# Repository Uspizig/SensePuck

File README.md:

# SensePuck: The Addon Board for the Seeed Round Display

## Features:

1. **AudioAmplifier MAX98357**: Listen to your favourite Tunes with an Audio Amplifier

2. **I2C Connector for Sensor**: Connect your favourite I2C Sensor board with the embedded 2.54mm connector

3. **Wireless Control**: Untehther your development process with the wireless capabilities. With WiFi and BLE, this tool allows remote control and data logging. Users can adjust settings and monitor data from a distance, offering a more flexible development experience.

4. **LIS3M Magentometer**: Check your Heading

5. **LSM6 Gyro+ACC**: Check Movements, Steps Pedometer

5. **Open Source & Programmable**: As an open-source device, the Device offers unmatched versatility. It is fully programmable, allowing you to tailor its functionality to your specific applications. This customization extends to software and hardware, opening up endless possibilities for creative and efficient project development.

6. **Compact Design**: Designed for convenience, the LoRaCam Board compact and sleek form factor allows for seamless integration into existing setups. Its compatibility with USB PD power sources and inline integration capability minimizes the need for additional equipment or extensive redesign, making it a versatile and user-friendly addition to any development environment.

7. **Display+Touchscreeen**: Monitor live the current status on the Seeed Display

8. **RTC**: RealTimeClock from the Seeed Display

9. **RGB LED**: Status LED

10. **Battery Charger** Use the Battery Charger on the Seeed Display

11. **Rotary Encoder** Perfect for switching the Radio Station

12.  BME680: Measure Temperature, Humidity, Air Pressure, TVOC, eCO² (might update to BME688 or BME690 soon)
    
## Specifications

Needed Libaries:

https://github.com/schreibfaul1/ESP32-audioI2S
https://github.com/pololu/lis3mdl-arduino
https://github.com/pololu/lsm6-arduino
https://github.com/Seeed-Projects/SeeedStudio_TFT_eSPI
https://github.com/Seeed-Projects/SeeedStudio_lvgl
https://github.com/Seeed-Studio/Seeed_Arduino_RoundDisplay

### Key Features:

### Future Developments:

AI Detection of objects and determine if the device shall sent the data via LoRa 

## Testing for Performance

At the heart of SensePuck's design is a commitment to reliability and performance. To ensure that SensePuck stands up to real-world demands, we subjected it to testing under use conditions.

## License

MIT License

Copyright (c) 2025 blue2monster

Permission is hereby granted, free of charge, to any person obtaining a copy
of this software and associated documentation files (the "Software"), to deal
in the Software without restriction, including without limitation the rights
to use, copy, modify, merge, publish, distribute, sublicense, and/or sell
copies of the Software, and to permit persons to whom the Software is
furnished to do so, subject to the following conditions:

The above copyright notice and this permission notice shall be included in all
copies or substantial portions of the Software.

THE SOFTWARE IS PROVIDED "AS IS", WITHOUT WARRANTY OF ANY KIND, EXPRESS OR
IMPLIED, INCLUDING BUT NOT LIMITED TO THE WARRANTIES OF MERCHANTABILITY,
FITNESS FOR A PARTICULAR PURPOSE AND NONINFRINGEMENT. IN NO EVENT SHALL THE
AUTHORS OR COPYRIGHT HOLDERS BE LIABLE FOR ANY CLAIM, DAMAGES OR OTHER
LIABILITY, WHETHER IN AN ACTION OF CONTRACT, TORT OR OTHERWISE, ARISING FROM,
OUT OF OR IN CONNECTION WITH THE SOFTWARE OR THE USE OR OTHER DEALINGS IN THE
SOFTWARE.

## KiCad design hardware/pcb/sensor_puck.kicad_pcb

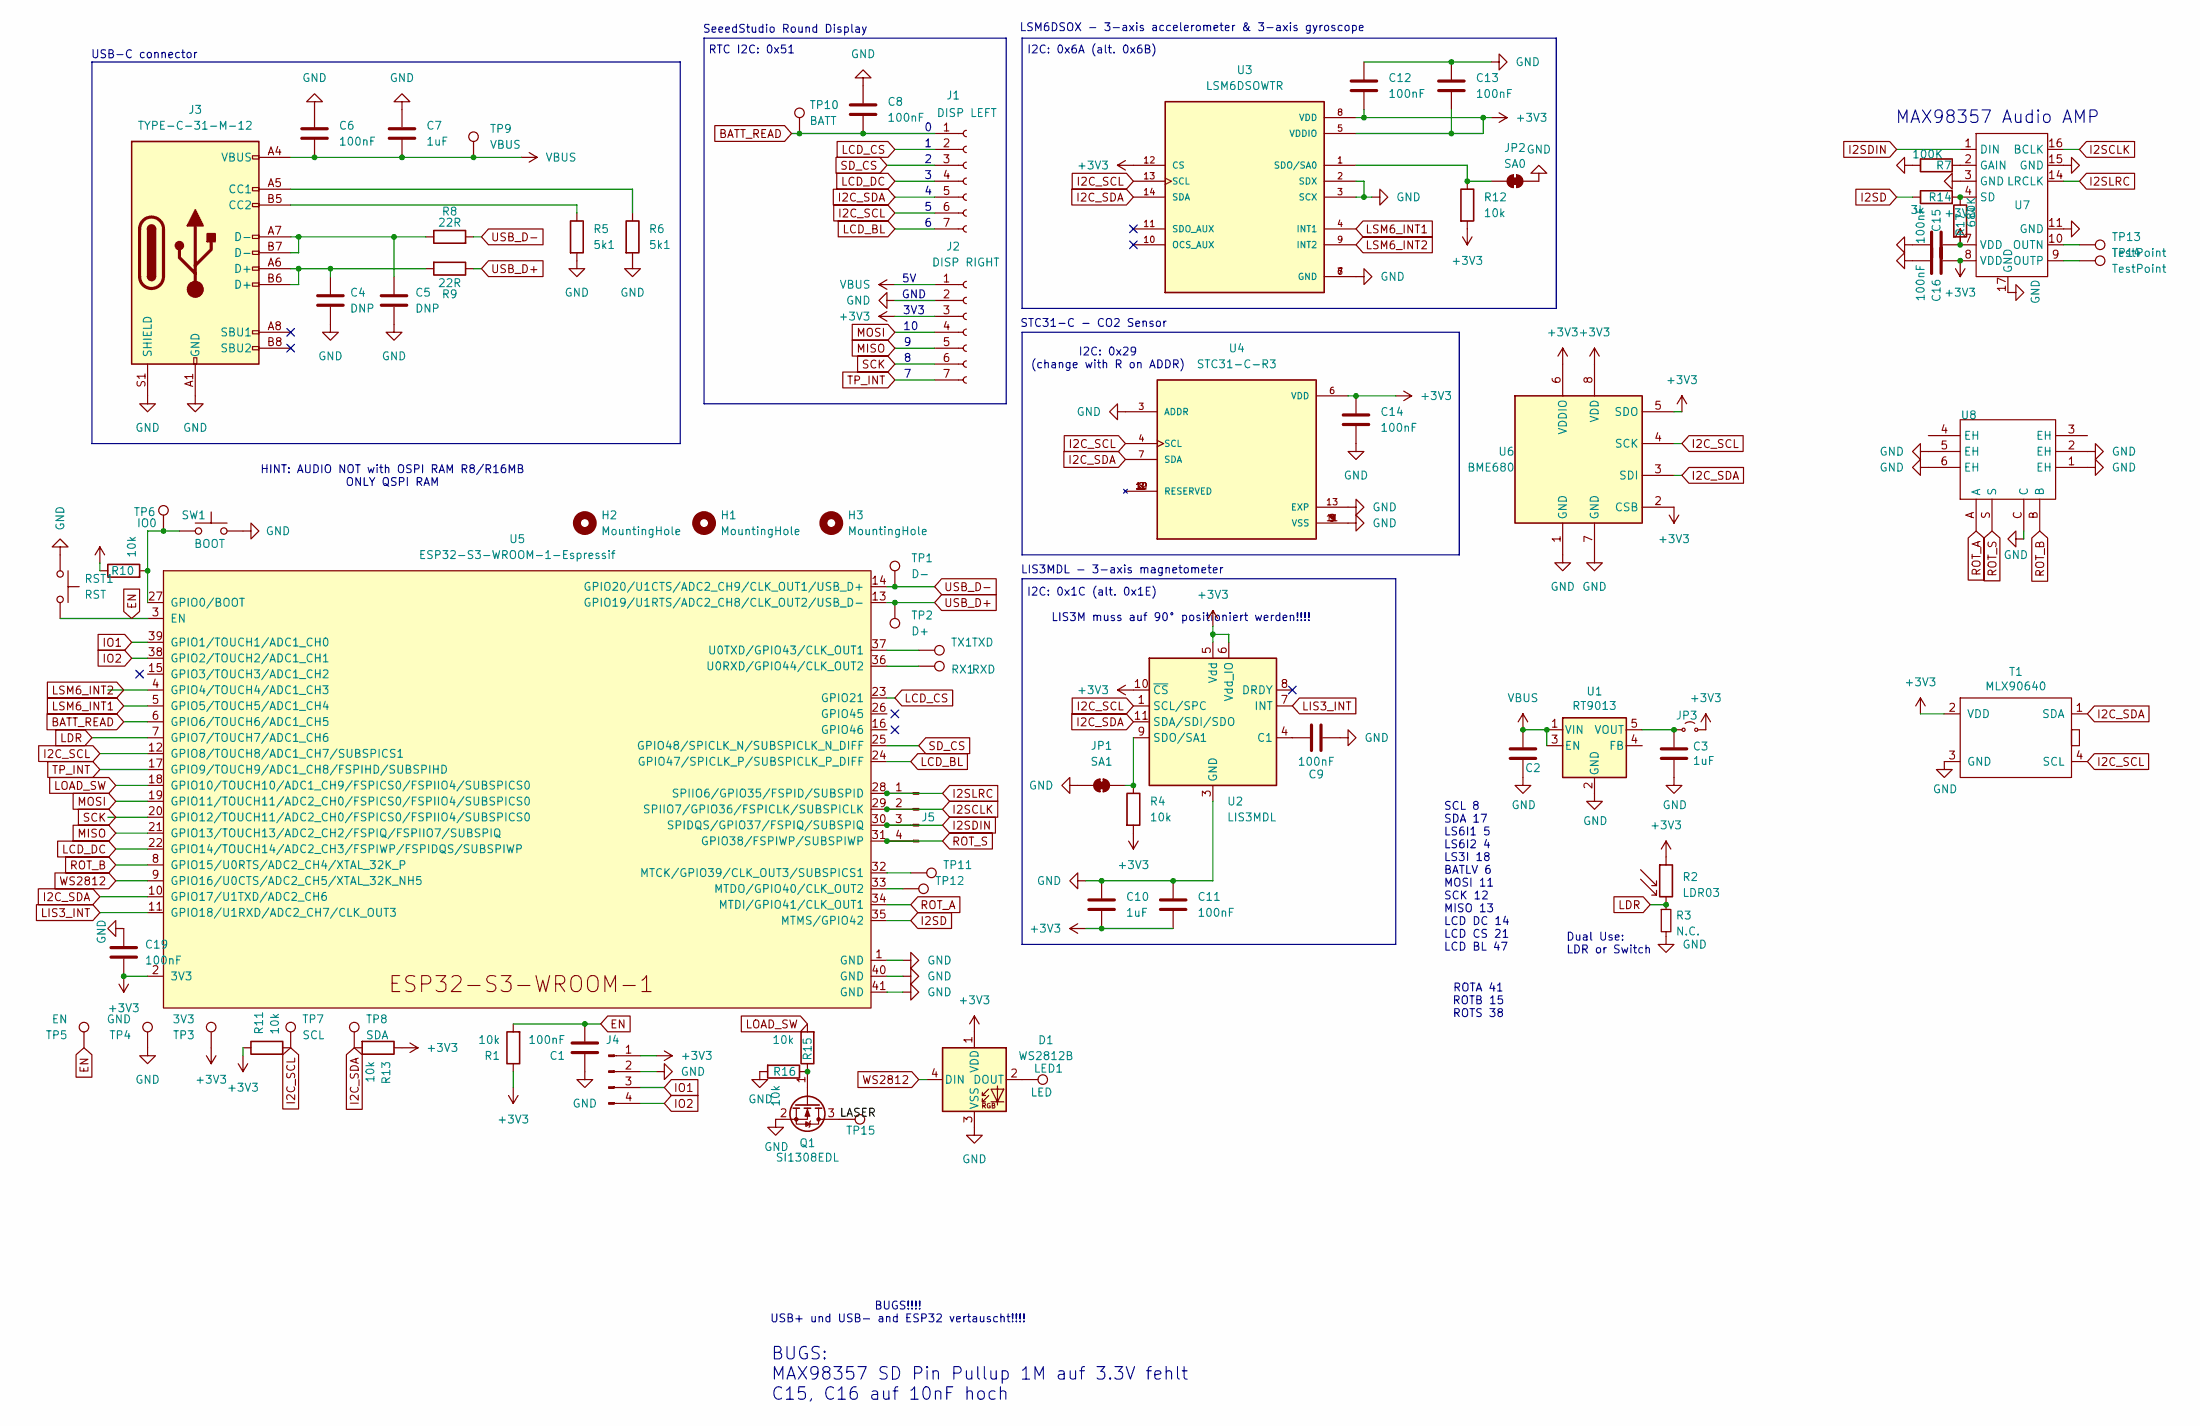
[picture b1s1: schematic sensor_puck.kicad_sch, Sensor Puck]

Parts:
C1, C6, C8, C9, C11, C12, C13, C14, C19: 100nF; C_0805_2012Metric
C2, C3: 1uF; C_0805_2012Metric_Pad1.18x1.45mm_HandSolder
C4, C5: DNP; C_0805_2012Metric
C7, C10: 1uF; C_0805_2012Metric
C15, C16: 100nF; C_0805_2012Metric_Pad1.18x1.45mm_HandSolder
D1: WS2812B; LED_WS2812B_PLCC4_5.0x5.0mm_P3.2mm
H1, H2: MountingHole; baerklein
H3: MountingHole; MountingHole_2.2mm_M2
J1: DISP LEFT; PinHeader_1x07_P2.54mm_Vertical
J2: DISP RIGHT; PinHeader_1x07_P2.54mm_Vertical
J3: TYPE-C-31-M-12; USB-C_SMD-TYPE-C-31-M-12
J4: Conn_01x04_Pin; PinHeader_1x04_P2.54mm_Vertical_SMD_Pin1Left
J5: Conn_01x04_Pin; PinHeader_1x04_P1.00mm_Vertical
JP1: SA1; SolderJumper-2_P1.3mm_Open_RoundedPad1.0x1.5mm
JP2: SA0; SolderJumper-2_P1.3mm_Open_RoundedPad1.0x1.5mm
JP3: Jumper_2_Small_Open; SolderJumper-2_P1.3mm_Open_RoundedPad1.0x1.5mm
LED1: LED; TestPoint_Pad_1.5x1.5mm
Q1: SI1308EDL; SOT-323_SC-70
R1, R15, R16: 10k; R_0603_1608Metric_Pad0.98x0.95mm_HandSolder
R2: LDR03; R_LDR_10x8.5mm_P7.6mm_Vertical
R3: N.C.; R_0805_2012Metric_Pad1.20x1.40mm_HandSolder
R4, R10, R11, R12, R13: 10k; R_0805_2012Metric
R5, R6: 5k1; R_0805_2012Metric
R7: 100K; R_0805_2012Metric_Pad1.20x1.40mm_HandSolder
R8, R9: 22R; R_0805_2012Metric
R14: 3k; R_0805_2012Metric_Pad1.20x1.40mm_HandSolder
R17: 680K; R_0805_2012Metric_Pad1.20x1.40mm_HandSolder
RST1: RST; SW_PUSH_6mm
RX1: RXD; TestPoint_Pad_1.0x1.0mm
SW1: BOOT; SW_PUSH_6mm
T1: MLX90640; Part Number 482-MLX90640ESFBABSP
TP1: D-; TestPoint_Pad_1.0x1.0mm
TP2: D+; TestPoint_Pad_1.0x1.0mm
TP3: 3V3; TestPoint_Pad_1.0x1.0mm
TP4: GND; TestPoint_Pad_1.0x1.0mm
TP5: EN; TestPoint_Pad_1.0x1.0mm
TP6: IO0; TestPoint_Pad_1.0x1.0mm
TP7: SCL; TestPoint_Pad_1.0x1.0mm
TP8: SDA; TestPoint_Pad_1.0x1.0mm
TP9: VBUS; TestPoint_Pad_1.0x1.0mm
TP10: BATT; TestPoint_Pad_1.0x1.0mm
TP11, TP12, TP13, TP14, TP15: TestPoint; TestPoint_Pad_D1.0mm
TX1: TXD; TestPoint_Pad_1.0x1.0mm
U1: RT9013; SOT-23-5
U2: LIS3MDL; LGA-12_2x2mm_P0.5mm
U3: LSM6DSOWTR; LGA-14_3x2.5mm_P0.5mm_LayoutBorder3x4y; PARTREV 3.0
U4: STC31-C-R3; XDCR_STC31-C-R3; PARTREV 3.2
U5: ESP32-S3-WROOM-1-Espressif; ESP32-S3-WROOM-1
U6: BME680; Bosch_LGA-8_3x3mm_P0.8mm_ClockwisePinNumbering
U7: TQFN-16_L3.0-W3.0-P0.50-BL-EP1.5
U8: SW-SMD_SIQ-02FVS3_1; Manufacturer Part SIQ-02FVS3; LCSC Part Name 拨轮滚轮旋转编码器开关

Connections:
+3V3: C10.2, C11.2, C12.2, C13.2, C14.1, C15.1, C16.1, C19.2, D1.1 (VDD), J2.3, J4.1, JP3.2 (B), R1.1, R2.1, R4.2, R10.1, R11.1, R12.2, R13.1, R17.2, T1.2 (VDD), TP3.1, U2.5 (Vdd), U2.6 (Vdd_IO), U2.10 (~CS), U3.5 (VDDIO), U3.8 (VDD), U3.12 (CS), U4.6 (VDD), U5.2 (3V3), U6.2 (CSB), U6.5 (SDO), U6.6 (VDDIO), U6.8 (VDD), U7.7 (VDD), U7.8 (VDD)
/LASER: Q1.3 (D), TP15.1; also elsewhere on the board
BATT_READ: C8.1, J1.1, TP10.1, U5.6 (GPIO6/TOUCH6/ADC1_CH5)
EN: C1.2, R1.2, RST1.2, TP5.1, U5.3 (EN); also elsewhere on the board
GND: C1.1, C2.1, C3.1, C4.2, C5.2, C6.1, C7.1, C8.2, C9.2, C10.1, C11.1, C12.1, C13.1, C14.2, C15.2, C16.2, C19.1, D1.3 (VSS), J2.2, J3.A1 (GND), J3.A12 (GND), J3.B1 (GND), J3.B12 (GND), J3.S1 (SHIELD), J4.2, JP1.1 (A), JP2.2 (B), Q1.2 (S), R3.2, R5.2, R6.2, R7.1, R16.2, RST1.1, SW1.2, T1.3 (GND), TP4.1, U1.2 (GND), U2.2 (GND), U2.3 (GND), U2.12 (GND), U3.2 (SDX), U3.3 (SCX), U3.6 (GND), U3.7 (GND), U4.1 (VSS), U4.3 (ADDR), U4.5 (VSS), U4.9 (VSS), U4.11 (VSS), U4.13 (EXP), U5.1 (GND), U5.40 (GND), U5.41 (GND), U6.1 (GND), U6.7 (GND), U7.3 (GND), U7.11 (GND), U7.15 (GND), U7.17 (GND), U8.1 (EH), U8.2 (EH), U8.5 (EH), U8.6 (EH), U8.C; also elsewhere on the board
I2C_SCL: J1.6, R11.2, T1.4 (SCL), TP7.1, U2.1 (SCL/SPC), U3.13 (SCL), U4.4 (SCL), U5.12 (GPIO8/TOUCH8/ADC1_CH7/SUBSPICS1), U6.4 (SCK)
I2C_SDA: J1.5, R13.2, T1.1 (SDA), TP8.1, U2.11 (SDA/SDI/SDO), U3.14 (SDA), U4.7 (SDA), U5.10 (GPIO17/U1TXD/ADC2_CH6), U6.3 (SDI)
I2SCLK: J5.2, U5.29 (SPIIO7/GPIO36/FSPICLK/SUBSPICLK), U7.16 (BCLK)
I2SD: R14.1, U5.35 (MTMS/GPIO42)
I2SDIN: J5.3, U5.30 (SPIDQS/GPIO37/FSPIQ/SUBSPIQ), U7.1 (DIN)
I2SLRC: J5.1, U5.28 (SPIIO6/GPIO35/FSPID/SUBSPID), U7.14 (LRCLK)
IO1: J4.3, U5.39 (GPIO1/TOUCH1/ADC1_CH0)
IO2: J4.4, U5.38 (GPIO2/TOUCH2/ADC1_CH1)
LCD_BL: J1.7, U5.24 (GPIO47/SPICLK_P/SUBSPICLK_P_DIFF)
LCD_CS: J1.2, U5.23 (GPIO21)
LCD_DC: J1.4, U5.22 (GPIO14/TOUCH14/ADC2_CH3/FSPIWP/FSPIDQS/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)
LDR: R2.2, R3.1, U5.7 (GPIO7/TOUCH7/ADC1_CH6)
LIS3_INT: U2.7 (INT), U5.11 (GPIO18/U1RXD/ADC2_CH7/CLK_OUT3)
LOAD_SW: R15.2, U5.18 (GPIO10/TOUCH10/ADC1_CH9/FSPICS0/FSPIIO4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)
LSM6_INT1: U3.4 (INT1), U5.5 (GPIO5/TOUCH5/ADC1_CH4)
LSM6_INT2: U3.9 (INT2), U5.4 (GPIO4/TOUCH4/ADC1_CH3)
MISO: J2.5, U5.21 (GPIO13/TOUCH13/ADC2_CH2/FSPIQ/FSPIIO7/S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)
MOSI: J2.4, U5.19 (GPIO11/TOUCH11/ADC2_CH0/FSPICS0/FSPIIO4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)
unnamed: C4.1, J3.A6 (D+), J3.B6 (D+), R9.2
unnamed: C5.1, J3.A7 (D-), J3.B7 (D-), R8.1
unnamed 25: D1.2 (DOUT), LED1.1; also elsewhere on the board
unnamed: J3.A5 (CC1), R6.1
unnamed: J3.B5 (CC2), R5.1
unnamed: JP1.2 (B), R4.1, U2.9 (SDO/SA1)
unnamed: JP2.1 (A), R12.1, U3.1 (SDO/SA0)
unnamed: C3.2, JP3.1 (A), U1.5 (VOUT)
unnamed: Q1.1 (G), R15.1, R16.1
unnamed: C9.1, U2.4 (C1)
unnamed: R10.2, SW1.1, TP6.1, U5.27 (GPIO0/BOOT)
unnamed: TP11.1, U5.32 (MTCK/GPIO39/CLK_OUT3/SUBSPICS1)
unnamed: TP12.1, U5.33 (MTDO/GPIO40/CLK_OUT2)
unnamed 36: RX1.1, U5.36 (U0RXD/GPIO44/CLK_OUT2); also elsewhere on the board
unnamed 37: TX1.1, U5.37 (U0TXD/GPIO43/CLK_OUT1); also elsewhere on the board
unnamed: R7.2, U7.2 (GAIN)
unnamed: TP13.1, U7.10 (OUTN)
unnamed: TP14.1, U7.9 (OUTP)
unnamed: R14.2, R17.1, U7.4 (SD)
ROT_A: U5.34 (MTDI/GPIO41/CLK_OUT1), U8.A
ROT_B: U5.8 (GPIO15/U0RTS/ADC2_CH4/XTAL_32K_P), U8.B
ROT_S: J5.4, U5.31 (GPIO38/FSPIWP/SUBSPIWP), U8.S
SCK: J2.6, U5.20 (GPIO12/TOUCH11/ADC2_CH0/FSPICS0/FSPIIO4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)
SD_CS: J1.3, U5.25 (GPIO48/SPICLK_N/SUBSPICLK_N_DIFF)
TP_INT: J2.7, U5.17 (GPIO9/TOUCH9/ADC1_CH8/FSPIHD/SUBSPIHD)
USB_D+: R9.1, TP2.1, U5.13 (GPIO19/U1RTS/ADC2_CH8/CLK_OUT2/USB_D-)
USB_D-: R8.2, TP1.1, U5.14 (GPIO20/U1CTS/ADC2_CH9/CLK_OUT1/USB_D+)
VBUS: C2.2, C6.2, C7.2, J2.1, J3.A4 (VBUS), J3.A9 (VBUS), J3.B4 (VBUS), J3.B9 (VBUS), TP9.1, U1.1 (VIN), U1.3 (EN)
WS2812: D1.4 (DIN), U5.9 (GPIO16/U0CTS/ADC2_CH5/XTAL_32K_NH5)

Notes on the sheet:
USB-C connector
BUGS: MAX98357 SD Pin Pullup 1M auf 3.3V fehlt C15, C16 auf 10nF hoch
LIS3M muss auf 90° positioniert werden!!!!
SeeedStudio Round Display
SCL 8 SDA 17 LS6I1 5 LS6I2 4 LS3I 18 BATLV 6 MOSI 11 SCK 12 MISO 13 LCD DC 14 LCD CS 21 LCD BL 47
I2C: 0x1C (alt. 0x1E)
RTC I2C: 0x51
Dual Use: LDR or Switch
I2C: 0x6A (alt. 0x6B)
BUGS!!!! USB+ und USB- and ESP32 vertauscht!!!!
LIS3MDL - 3-axis magnetometer
STC31-C - CO2 Sensor
GND
LSM6DSOX - 3-axis accelerometer & 3-axis gyroscope
ROTA 41 ROTB 15 ROTS 38
3V3
I2C: 0x29 (change with R on ADDR)
MAX98357 Audio AMP
HINT: AUDIO NOT with OSPI RAM R8/R16MB ONLY QSPI RAM

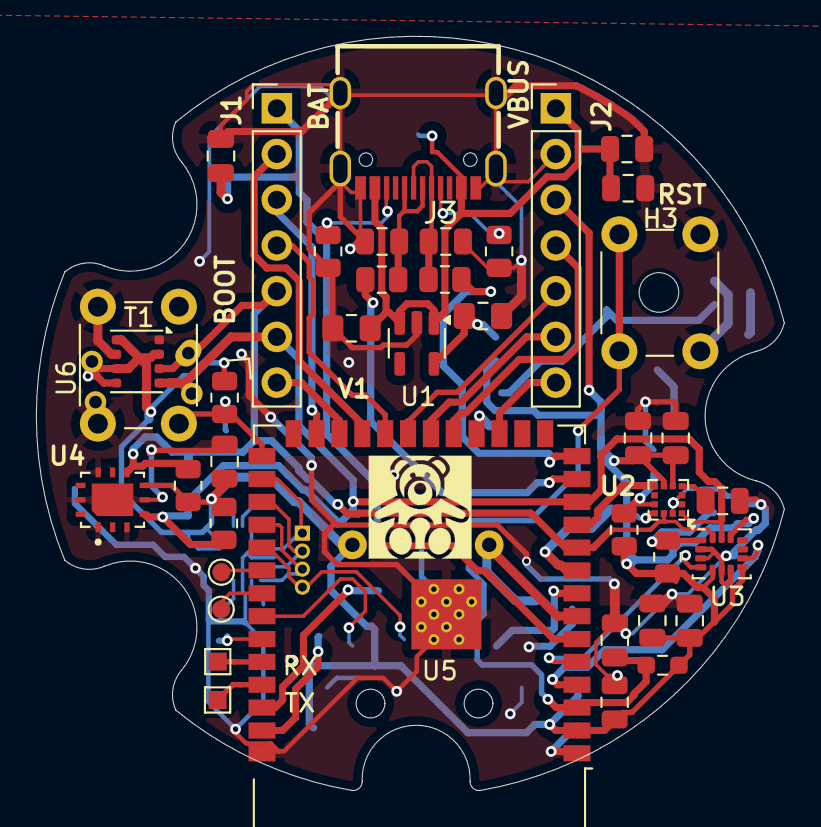
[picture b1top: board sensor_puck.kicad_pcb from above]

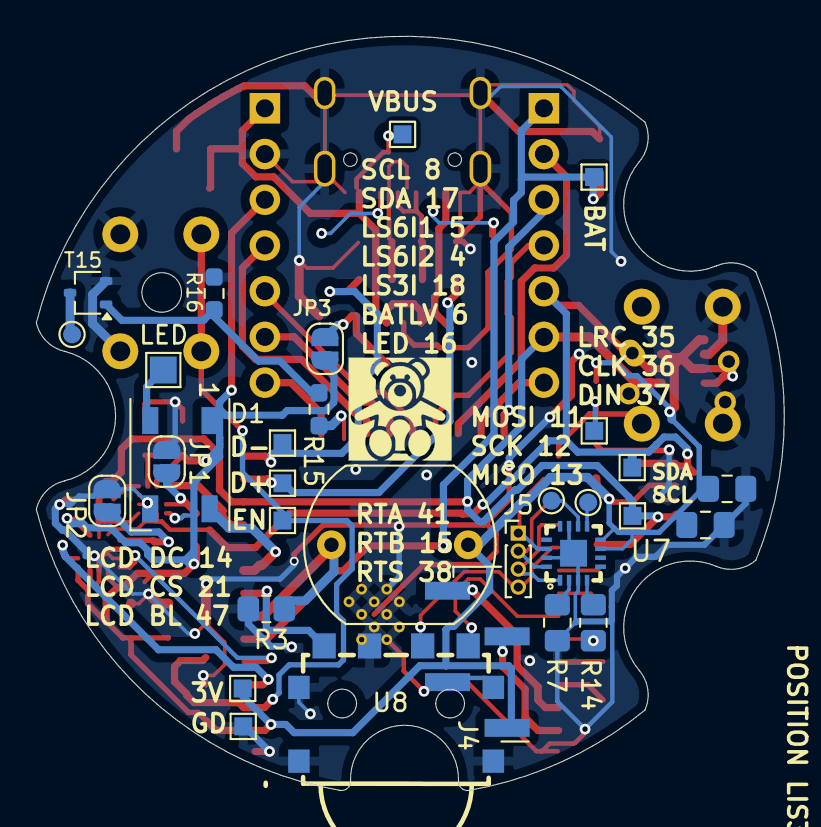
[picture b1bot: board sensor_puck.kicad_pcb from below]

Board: 2 copper layers, 41.6 x 41.9 mm, 75 parts (32 on the bottom side), 52 nets.

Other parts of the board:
LED: LED; TestPoint_Pad_1.5x1.5mm
RST: RST; SW_PUSH_6mm
RX: RXD; TestPoint_Pad_1.0x1.0mm
T15: TestPoint; TestPoint_Pad_D1.0mm
TX: TXD; TestPoint_Pad_1.0x1.0mm

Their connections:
/LASER: T15.1; also elsewhere on the board
EN: RST.2; also elsewhere on the board
GND: RST.1; also elsewhere on the board
unnamed 25: LED.1; also elsewhere on the board
unnamed 36: RX.1; also elsewhere on the board
unnamed 37: TX.1; also elsewhere on the board

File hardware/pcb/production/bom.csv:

Designator,Footprint,Quantity,Value,LCSC Part #
"C1, C11, C12, C13, C14, C15, C16, C19, C6, C8, C9",0805,11,100nF,
"C10, C2, C3, C7",0805,4,1uF,
"C4, C5",0805,2,DNP,
D1,LED_WS2812B_PLCC4_5.0x5.0mm_P3.2mm,1,WS2812B,
J1,PinHeader_1x07_P2.54mm_Vertical,1,DISP LEFT,
J2,PinHeader_1x07_P2.54mm_Vertical,1,DISP RIGHT,
J3,USB-C_SMD-TYPE-C-31-M-12,1,TYPE-C-31-M-12,
J4,PinHeader_1x04_P2.54mm_Vertical_SMD_Pin1Left,1,Conn_01x04_Pin,
J5,PinHeader_1x04_P1.00mm_Vertical,1,Conn_01x04_Pin,
JP3,SolderJumper-2_P1.3mm_Open_RoundedPad1.0x1.5mm,1,Jumper_2_Small_Open,
LED,TestPoint_Pad_1.5x1.5mm,1,LED,
Q1,SOT-323_SC-70,1,SI1308EDL,
"R1, R15, R16",0603,3,10k,
"R10, R11, R12, R13, R4",0805,5,10k,
R14,0805,1,300k,
R2,R_LDR_10x8.5mm_P7.6mm_Vertical,1,LDR03,
R3,0805,1,N.C.,
"R5, R6",0805,2,5k1,
R7,0805,1,100K,
"R8, R9",0805,2,22R,
RST,SW_PUSH_6mm,1,RST,
RX,TestPoint_Pad_1.0x1.0mm,1,RXD,
SW1,SW_PUSH_6mm,1,BOOT,
T1,MLX90640,1,MLX90640,
"T15, TP11, TP12, TP13, TP14",TestPoint_Pad_D1.0mm,5,TestPoint,
TP1,TestPoint_Pad_1.0x1.0mm,1,D-,
TP10,TestPoint_Pad_1.0x1.0mm,1,BATT,
TP2,TestPoint_Pad_1.0x1.0mm,1,D+,
TP3,TestPoint_Pad_1.0x1.0mm,1,3V3,
TP4,TestPoint_Pad_1.0x1.0mm,1,GND,
TP5,TestPoint_Pad_1.0x1.0mm,1,EN,
TP6,TestPoint_Pad_1.0x1.0mm,1,IO0,
TP7,TestPoint_Pad_1.0x1.0mm,1,SCL,
TP8,TestPoint_Pad_1.0x1.0mm,1,SDA,
TP9,TestPoint_Pad_1.0x1.0mm,1,VBUS,
TX,TestPoint_Pad_1.0x1.0mm,1,TXD,
U1,SOT-23-5,1,RT9013,
U2,LGA-12_2x2mm_P0.5mm,1,LIS3MDL,
U3,LGA-14_3x2.5mm_P0.5mm_LayoutBorder3x4y,1,LSM6DSOWTR,
U4,XDCR_STC31-C-R3,1,STC31-C-R3,
U5,ESP32-S3-WROOM-1,1,ESP32-S3-WROOM-1-Espressif,
U6,Bosch_LGA-8_3x3mm_P0.8mm_ClockwisePinNumbering,1,BME680,
U7,TQFN-16_L3.0-W3.0-P0.50-BL-EP1.5,1,~,
U8,SW-SMD_SIQ-02FVS3_1,1,~,

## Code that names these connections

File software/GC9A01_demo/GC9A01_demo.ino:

#include <SPI.h>
#include "USB.h"
#include "GC9A01.h"

#include <Wire.h>


//SEEED DISPLAY

#define RES 0
#define DC  14
#define CS  21
#define SCK  12
#define MISO  13
#define MOSI  11
#define SS  21
#define BLK 47

#define SDA2 17
#define SCL2 8

#define LCD_CS 21
#define LCD_MOSI 11
#define LCD_MISO 13
#define LCD_SCK 12
#define LCD_DC 14
#define LCD_BL 47
#define SD_CS 48
#define TOUCH_INT 9
#define BAT_READ 6

USBCDC USBSerial;

void GC9A01_set_reset(uint8_t val) {
    digitalWrite(RES, val);
}

void GC9A01_set_data_command(uint8_t val) {
    digitalWrite(DC, val);
}

void GC9A01_set_chip_select(uint8_t val) {
    digitalWrite(CS, val);
}

void GC9A01_spi_tx(uint8_t *data, size_t len) {
    while (len--) {
        SPI.transfer(*data);
        data++;
    }
}

void GC9A01_delay(uint16_t ms) {
    delay(ms);
}

void setup() {
    
    
    USBSerial.begin();USB.begin();
    pinMode(BLK, OUTPUT);
    pinMode(RES, OUTPUT);
    pinMode(DC, OUTPUT);
    pinMode(CS, OUTPUT);
    USBSerial.println("Pin Mode Set");
    //SPI.begin(22, 21);
    digitalWrite(BLK, 1);
    USBSerial.println("Pin Set BLK");
    SPI.begin(SCK, MISO, MOSI, SS);
    USBSerial.println("SPI Begin erledigt");
    USBSerial.println("Booting");
    GC9A01_init();
    struct GC9A01_frame frame = {{0,0},{239,239}};
    GC9A01_set_frame(frame);
    Wire.begin(SDA2, SCL2);
}

void loop() {
    scani2c();
    uint8_t color[3];

    // Triangle
    color[0] = 0xFF;
    color[1] = 0xFF;
    

    // Checkerboard
    USBSerial.println("Schachbrett");
    for (int x = 0; x < 240; x++) {
        for (int y = 0; y < 240; y++) {
            if ((x / 10) % 2 ==  (y / 10) % 2) {
                color[0] = 0xFF;
                color[1] = 0xFF;
                color[2] = 0xFF;
            } else {
                color[0] = 0x00;
                color[1] = 0x00;
                color[2] = 0x00;
            }
            if (x == 0 && y == 0) {
                GC9A01_write(color, sizeof(color));
            } else {
                GC9A01_write_continue(color, sizeof(color));
            }
        }
    }

    delay(1000);

    // Swiss flag
    USBSerial.println("Swiss flag");
    color[0] = 0xFF;
    for (int x = 0; x < 240; x++) {
        for (int y = 0; y < 240; y++) {
            if ((x >= 1*48 && x < 4*48 && y >= 2*48 && y < 3*48) ||
                (x >= 2*48 && x < 3*48 && y >= 1*48 && y < 4*48)) {
                color[1] = 0xFF;
                color[2] = 0xFF;
            } else {
                color[1] = 0x00;
                color[2] = 0x00;
            }
            if (x == 0 && y == 0) {
                GC9A01_write(color, sizeof(color));
            } else {
                GC9A01_write_continue(color, sizeof(color));
            }
        }
    }

    delay(1000);

}

void scani2c(void){
 byte error, address;
  int nDevices;
  USBSerial.println("Scanning...");
  nDevices = 0;
  for(address = 1; address < 127; address++ ) {
    Wire.beginTransmission(address);
    error = Wire.endTransmission();
    if (error == 0) {
      USBSerial.print("I2C device found at address 0x");
      if (address<16) {
        USBSerial.print("0");
      }
      USBSerial.println(address,HEX);
      nDevices++;
    }
    else if (error==4) {
      USBSerial.print("Unknow error at address 0x");
      if (address<16) {
        USBSerial.print("0");
      }
      USBSerial.println(address,HEX);
    }    
  }
  if (nDevices == 0) {
    USBSerial.println("No I2C devices found\n");
  }
  else {
    USBSerial.println("done\n");
  }
  delay(5000);          
}

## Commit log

2025-06-20 Create PCB - V3
